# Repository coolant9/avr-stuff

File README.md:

# avr-stuff
experiments on arduino and avr

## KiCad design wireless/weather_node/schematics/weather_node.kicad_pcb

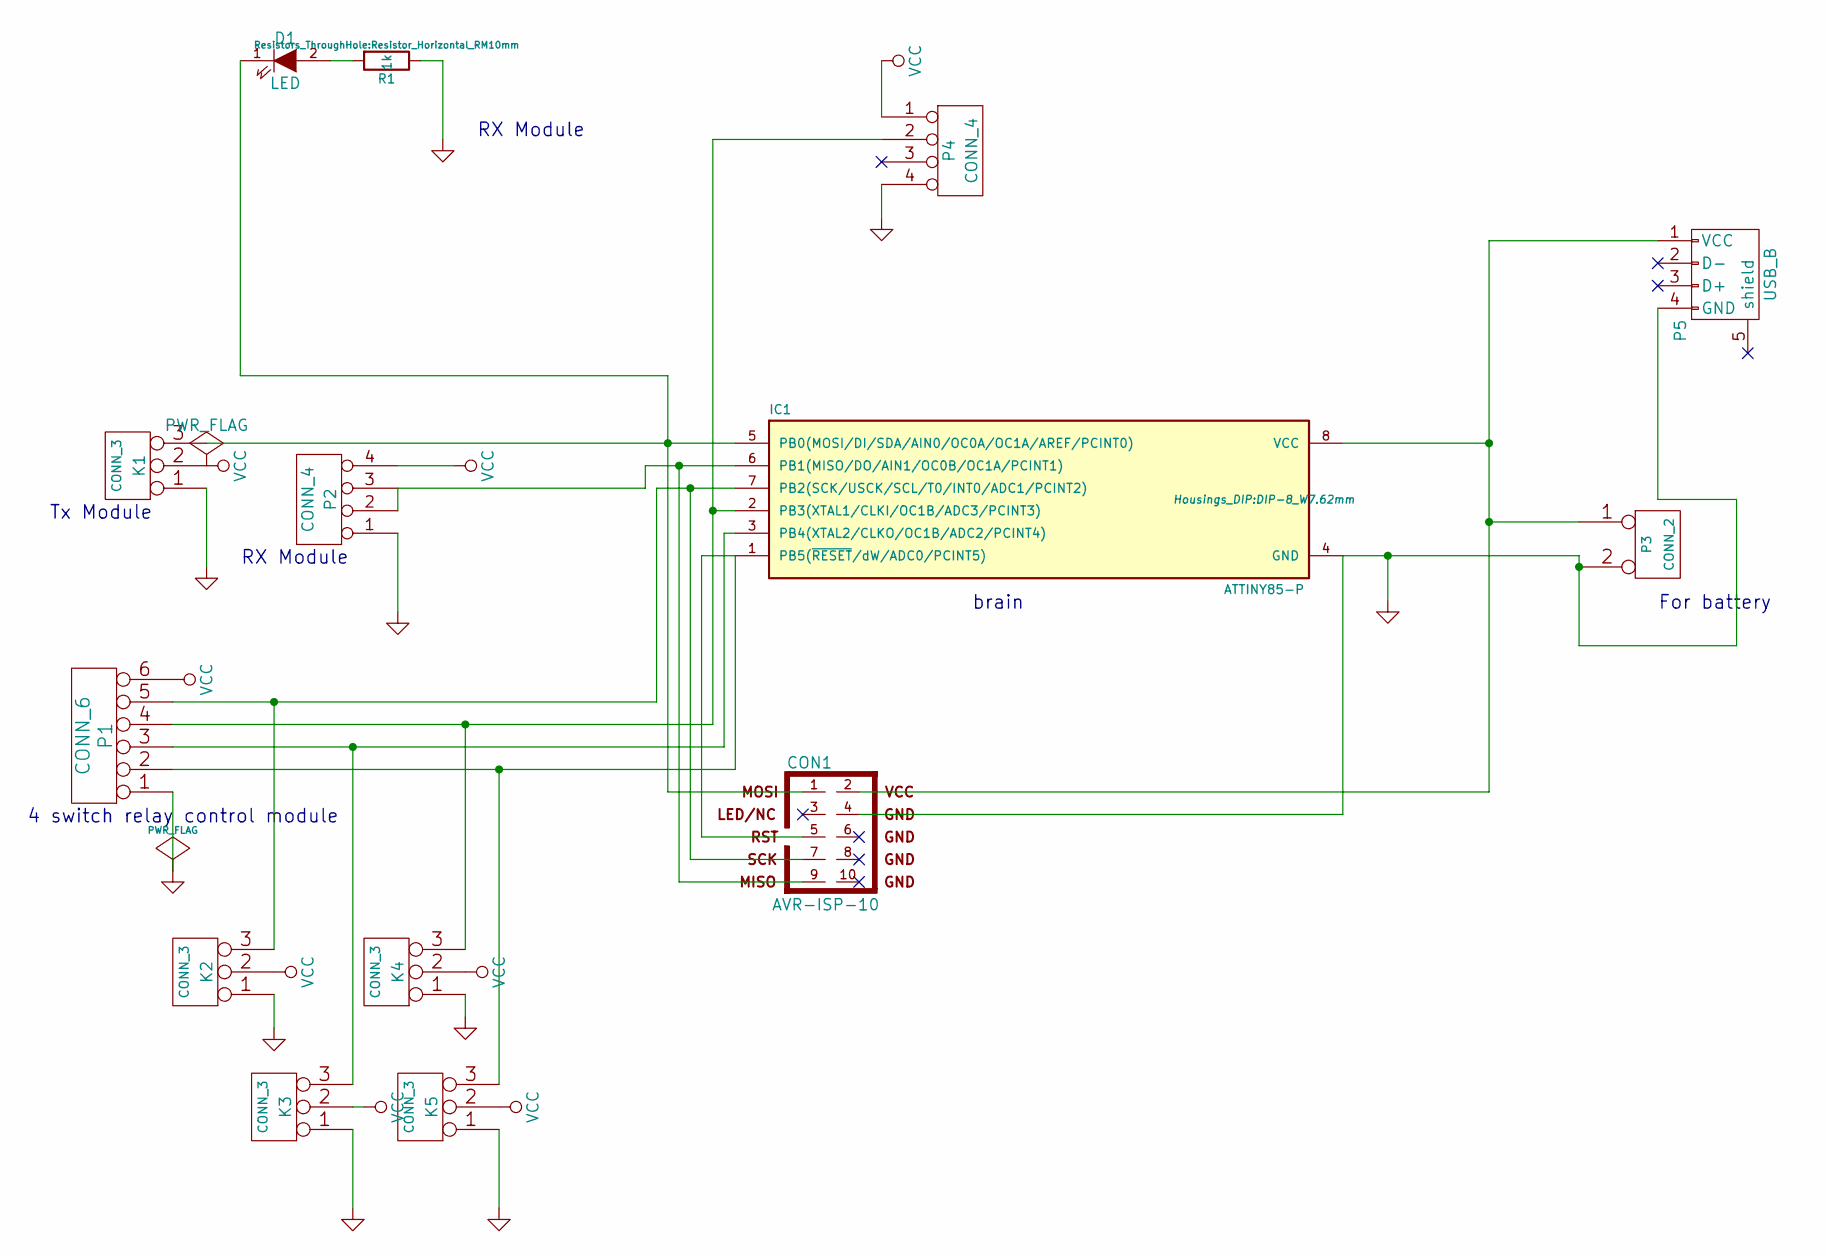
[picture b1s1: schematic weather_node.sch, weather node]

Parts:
CON1: AVR-ISP-10; Pin_Header_Straight_2x05
D1: LED; LED-5MM
IC1: ATTINY85-P; DIP-8_W7.62mm
K1, K2, K3, K4, K5: CONN_3; Pin_Header_Straight_1x03
P1: CONN_6; Pin_Header_Straight_1x06
P2, P4: CONN_4; Pin_Header_Straight_1x04
P3: CONN_2; Pin_Header_Straight_1x02
P5: USB_B
R1: 1k; Resistor_Horizontal_RM10mm

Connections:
GND: CON1.4, IC1.4 (GND), K1.1, K2.1, K3.1, K4.1, K5.1, P1.1, P2.1, P3.2 (PM), P4.4, P5.4 (GND), R1.1
unnamed: CON1.1, D1.1 (K), IC1.5 (PB0(MOSI/DI/SDA/AIN0/OC0A/OC1A/AREF/PCI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), K1.3
unnamed: CON1.2, IC1.8 (VCC), P3.1, P5.1 (VCC)
unnamed: CON1.5, IC1.1 (PB5(~RESET~/dW/ADC0/PCINT5)), K5.3, P1.2
unnamed: CON1.7, IC1.7 (PB2(SCK/USCK/SCL/T0/INT0/ADC1/PCINT2)), K2.3, P1.5
unnamed: CON1.9, IC1.6 (PB1(MISO/DO/AIN1/OC0B/OC1A/PCINT1)), P2.2, P2.3
unnamed: D1.2 (A), R1.2
unnamed: IC1.2 (PB3(XTAL1/CLKI/OC1B/ADC3/PCINT3)), K4.3, P1.4, P4.2
unnamed: IC1.3 (PB4(XTAL2/CLKO/OC1B/ADC2/PCINT4)), K3.3, P1.3
VCC: K1.2 (PM), K2.2 (PM), K3.2 (PM), K4.2 (PM), K5.2 (PM), P1.6, P2.4, P4.1

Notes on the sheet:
brain
4 switch relay control module
RX Module
Tx Module
For battery

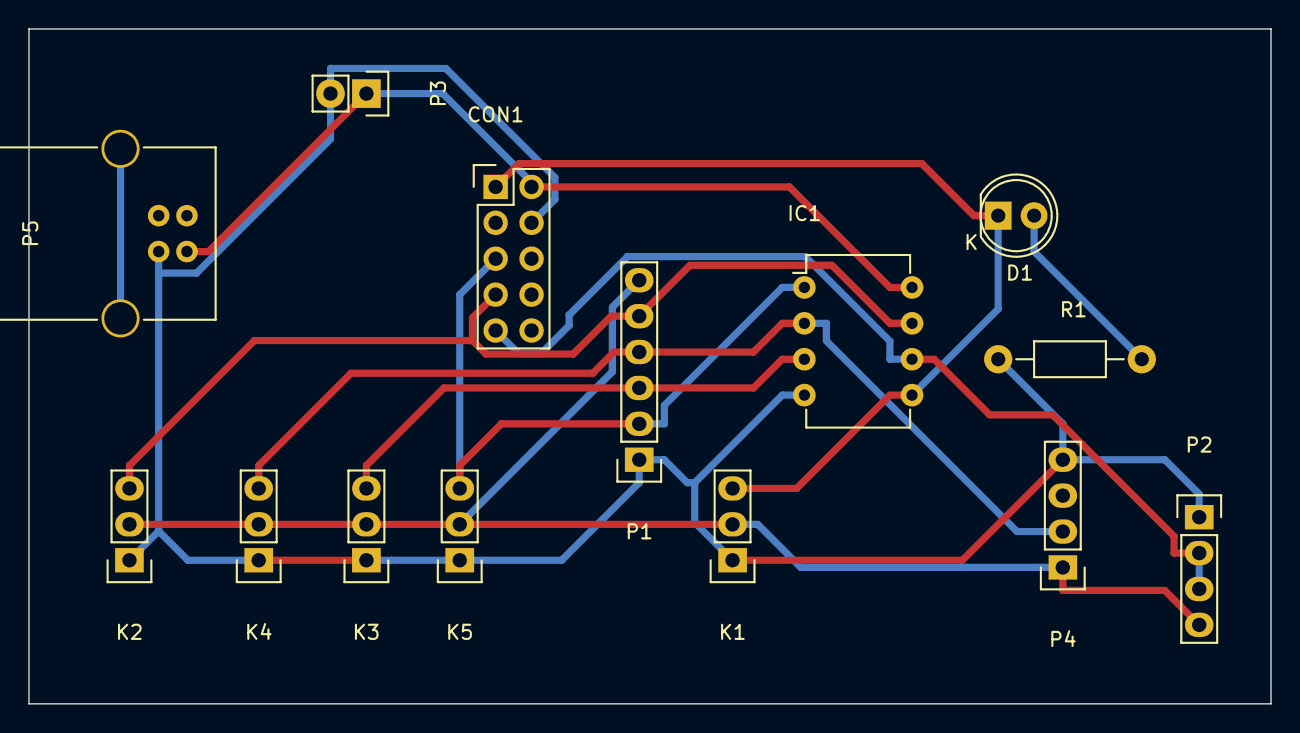
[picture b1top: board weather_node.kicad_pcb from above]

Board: 2 copper layers, 87.9 x 47.8 mm, 14 parts (0 on the bottom side), 10 nets.

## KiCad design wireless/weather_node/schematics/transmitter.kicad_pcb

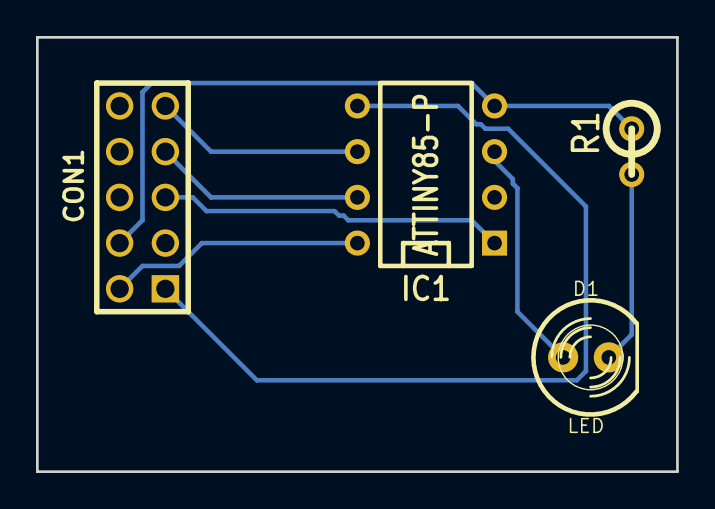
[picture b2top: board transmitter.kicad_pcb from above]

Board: 2 copper layers, 35.6 x 24.1 mm, 4 parts (0 on the bottom side), 8 nets.

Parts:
CON1: AVR-ISP-10; PIN_ARRAY_5x2
D1: LED; LED-5MM
IC1: ATTINY85-P; DIP-8__300
R1: 1k; R1

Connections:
GND: CON1.4, IC1.4, R1.1
unnamed: D1.1, IC1.3
unnamed: CON1.1, IC1.5
unnamed: CON1.9, IC1.6
unnamed: CON1.7, IC1.7
unnamed: CON1.5, IC1.1
unnamed: D1.2, R1.2
VCC: CON1.2, IC1.8

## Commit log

2017-09-26 Interfacing with UART.
2017-09-26 Geting the interface wth DHT temprature and humidity sensor working.
2017-09-26 Sending the data aquired over DHT11 sensor over 433 Mhz transcievers using virtual wire.
